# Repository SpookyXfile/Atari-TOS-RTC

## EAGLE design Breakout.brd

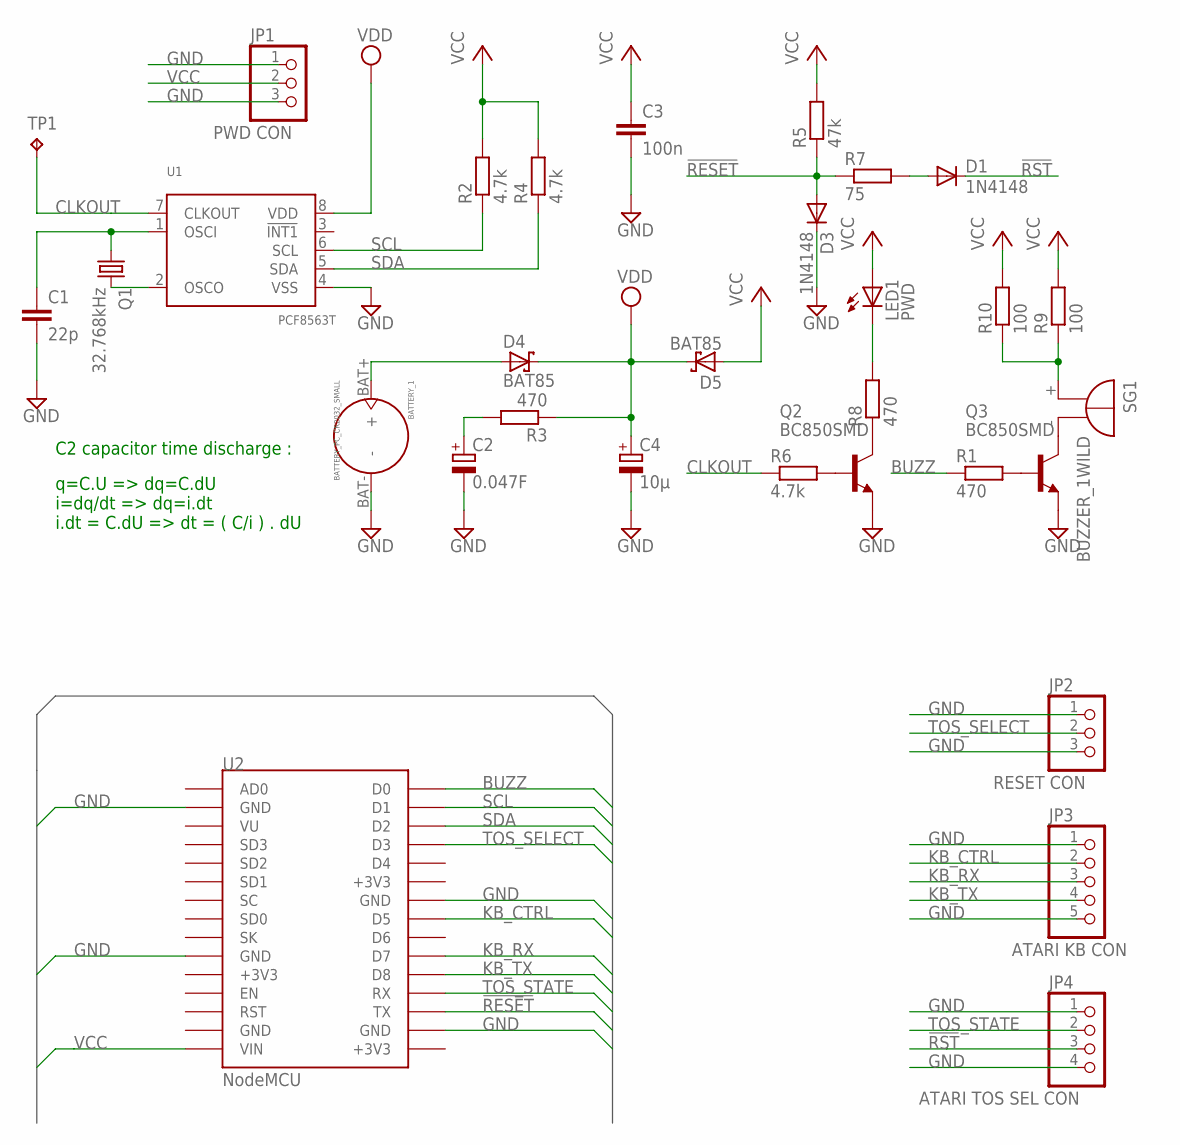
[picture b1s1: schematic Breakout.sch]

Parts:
BATTERY_1: BATTERY_PC_CR2032_SMALL; BATTERY_1236_SMALL
C1: 22p; C025-024X044
C2: 0.047F; SCAP1
C3: 100n; C050-025X075
C4: 10µ; E2-5
D1: 1N4148; DO35-5
D3: 1N4148; DO35-7
D4, D5: BAT85; DO41-10
JP1: PWD CON; 1X03
JP2: RESET CON; 1X03
JP3: ATARI KB CON; 1X05
JP4: ATARI TOS SEL CON; 1X04
LED1: PWD; LED5MM
Q1: 32.768kHz; TC38H
Q2, Q3: BC850SMD; SOT23-BEC
R1, R8: 470; M2012
R2, R4, R6: 4.7k; 0204/7
R3: 470; 0204/7
R5: 47k; 0204/7
R7: 75; 0204/7
R9: 100; M2012
R10: 100; 0207/7
SG1: BUZZER_1WILD; F/QMBIII-W
TP1: TPTP19SQ; TP19SQ
U1: PCF8563T; SOT96-1
U2: NodeMCU; NODE_MCU_V3_WILD_DIL

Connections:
!RESET: D3.A, R5.1, R7.1, U2.TX
!RST: D1.C, JP4.3
BUZZ: R1.1, U2.D0
CLKOUT: R6.1, TP1.TP, U1.7 (CLKOUT)
GND: BATTERY_1.BAT- (-), C1.2, C2.-, C3.2, C4.-, D3.C, JP1.1, JP1.3, JP2.1, JP2.3, JP3.1, JP3.5, JP4.1, JP4.4, Q2.E, Q3.E, U1.4 (VSS), U2.GND, U2.GND@0 (GND), U2.GND@2 (GND), U2.GND@3 (GND)
KB_CTRL: JP3.2, U2.D5
KB_RX: JP3.3, U2.D7
KB_TX: JP3.4, U2.D8
unnamed: C1.1, Q1.1, U1.1 (OSCI)
unnamed: Q1.2, U1.2 (OSCO)
unnamed: Q2.B, R6.2
unnamed: LED1.K (C), R8.2
unnamed: Q2.C, R8.1
unnamed: Q3.B, R1.2
unnamed: BATTERY_1.BAT+ (+), D4.A
unnamed: C2.+, R3.2
unnamed: Q3.C, SG1.-
unnamed: D1.A, R7.2
unnamed: R9.1, R10.1, SG1.+
SCL: R2.1, U1.6 (SCL), U2.D1
SDA: R4.1, U1.5 (SDA), U2.D2
TOS_SELECT: JP2.2, U2.D3
TOS_STATE: JP4.2, U2.RX
VCC: C3.1, D5.A, JP1.2, LED1.A, R2.2, R4.2, R5.2, R9.2, R10.2, U2.VIN
VDD: C4.+, D4.C, D5.C, R3.1, U1.8 (VDD)

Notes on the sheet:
C2 capacitor time discharge :
q=C.U => dq=C.dU i=dq/dt => dq=i.dt i.dt = C.dU => dt = ( C/i ) . dU

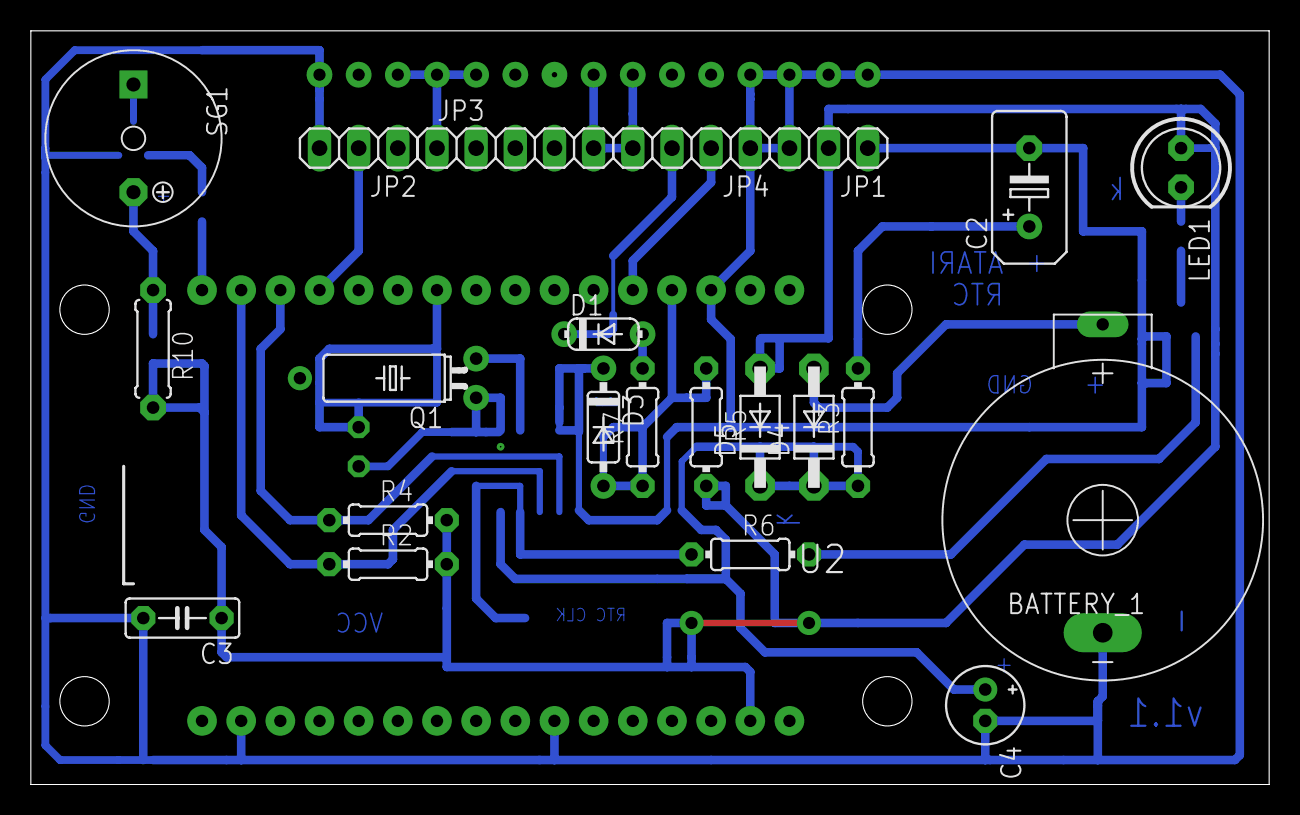
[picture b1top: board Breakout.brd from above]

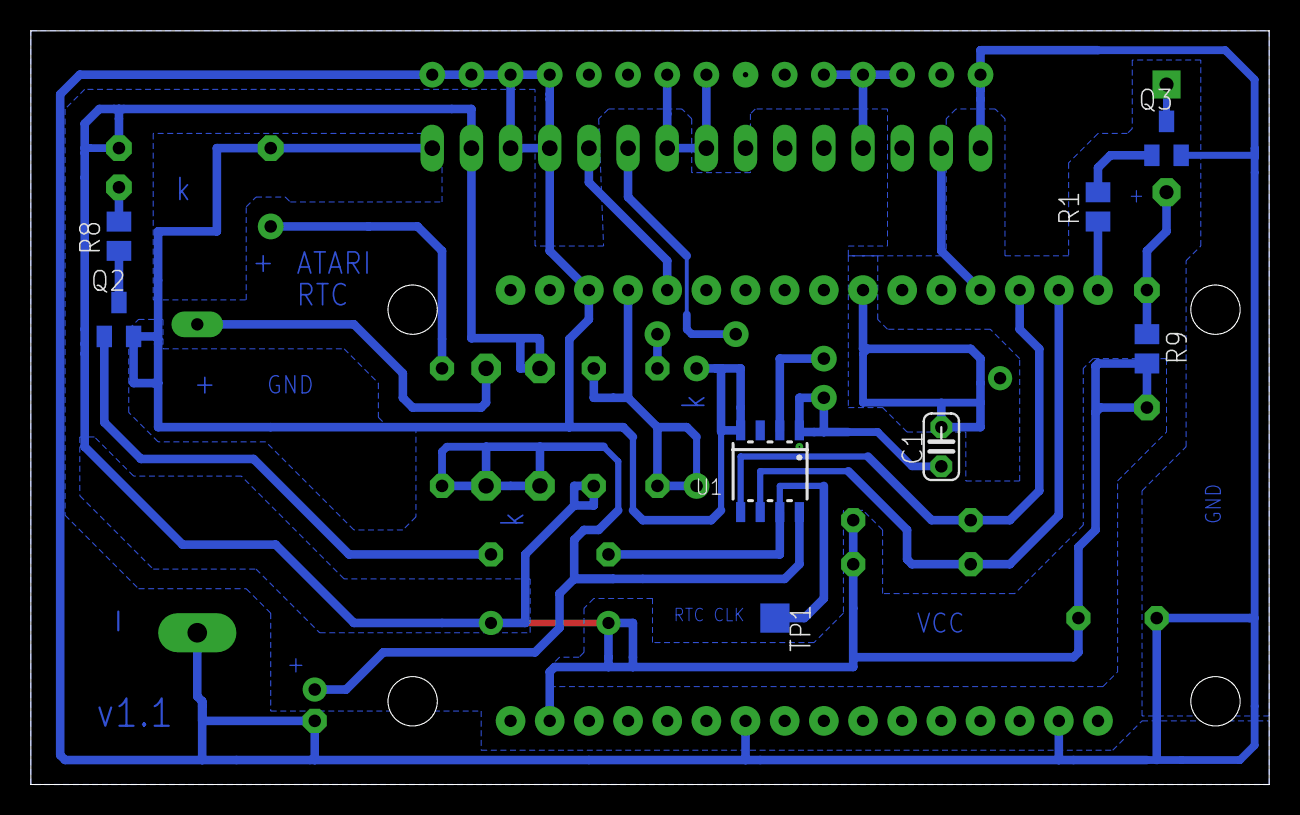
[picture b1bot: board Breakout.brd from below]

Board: 2 copper layers, 80.3 x 48.9 mm, 31 parts (8 on the bottom side), 25 nets.

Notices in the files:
parts and their libraries:
NXP_60_26022015: This library may be distributed and adapted freely for any purpose, as long as NXP is credited and any new creation is licensed under the same terms.
